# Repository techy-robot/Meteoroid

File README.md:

# Meteoroid

Production-ready 3d printer based on a Ender 5 frame, with multifunction tool changing, bed changing, and accessories with robots.

Preview Picture

Latest V0.7.0 [Onshape Link](https://cad.onshape.com/documents/1de0655c0501c319c0be82e5/v/c2a582b56fbe86c2e3bf18a1/e/f03e8779d1a8cc2741025c01)

It is desktop machine with plug and play heads. Chain these machines together and add robot carriages in between and you got yourself an awesome modular factory that can fit on a bench. The cost of the _entire system_ will likely be several thousand dollars, with the main machine between $300 to $500. I aim to lower the cost of a complete industrial system as much as possible.

The base machine is a CoreXY printer with a 500+mm/s move speed 30k+ accel, and 4 tool changer slots. The printer can be partially enclosed, with openings for robots to quick swap tools and beds and sometimes even sub-tools (Like a PnP head with different nozzle sizes). Software-wise, it will be running Klipper, which can interface with other software like OpenPNP using macros and linux ports.

Features:
- Standard 235mm x 235mm heated bed size with Garolyte bed for easy print release, supported by dual z-axis motors to provide stabilty without the complexity of an automatic leveling trimotor bed.
- Klipper
- Tool changer with 4 slots
- CoreXY
- Medium cost desktop production system
- Completely Open-Source
- 3 Accessory slots for extra toolhead elements like PnP heads or a camera
- Off-the-shelf components that are well known and high-quality, with many parts 3D printed in ASA
- Optional enclosure
- High print speed 500mm/s and 30k accel

I also designed a little adapter board I called Klipper to CACKLE. It basically takes USB-c input and 24v power, and converts this to my [CACKLE](https://github.com/techy-robot/CACKLE) layout spec and RS485 communication protocal. It uses a CH32 chip to process the commands and output equivalent Luos spec datapackets over the bus to my system.

# Building
I don't have specific build instructions yet as that takes a lot more development time, but you can reference the [BOM](https://github.com/techy-robot/Meteoroid/blob/main/BOM_Main%20assembly_simplified.csv) and the CAD file/Onshape to get all the parts and build it.

# Development Log
This project was worked on sporadically since Feb 1, 2025

See [Changelog](https://github.com/techy-robot/Meteoroid/blob/main/Changelog.md) for my full development log and the nitty-gritty details

# Credits
The motion system inspiration is from [Zero G Mercury 1.1](https://docs.zerog.one/manual/build/mercury_eva), which is a relatively simple corexy conversion for ender 5-style frames. I have tweaked many of the parts to fix small issues I noticed, revamped the frame with supports, added a toolchanging solution, and a 2 axis bed leveling system instead of the more costly 3-axis Hydra solution. The toolchanger is similar to the [Daksh V2](https://github.com/ankurv2k6/daksh-toolchanger-v2/) solution, except with a simpler single lock system, and concentric kinematic mount points instead of asymetrical contact mounts.

Everything else should be my own design, from the upcoming bed changing solution, upcoming robotic arms, toolheads, and the asteroid texture used on some of the parts.

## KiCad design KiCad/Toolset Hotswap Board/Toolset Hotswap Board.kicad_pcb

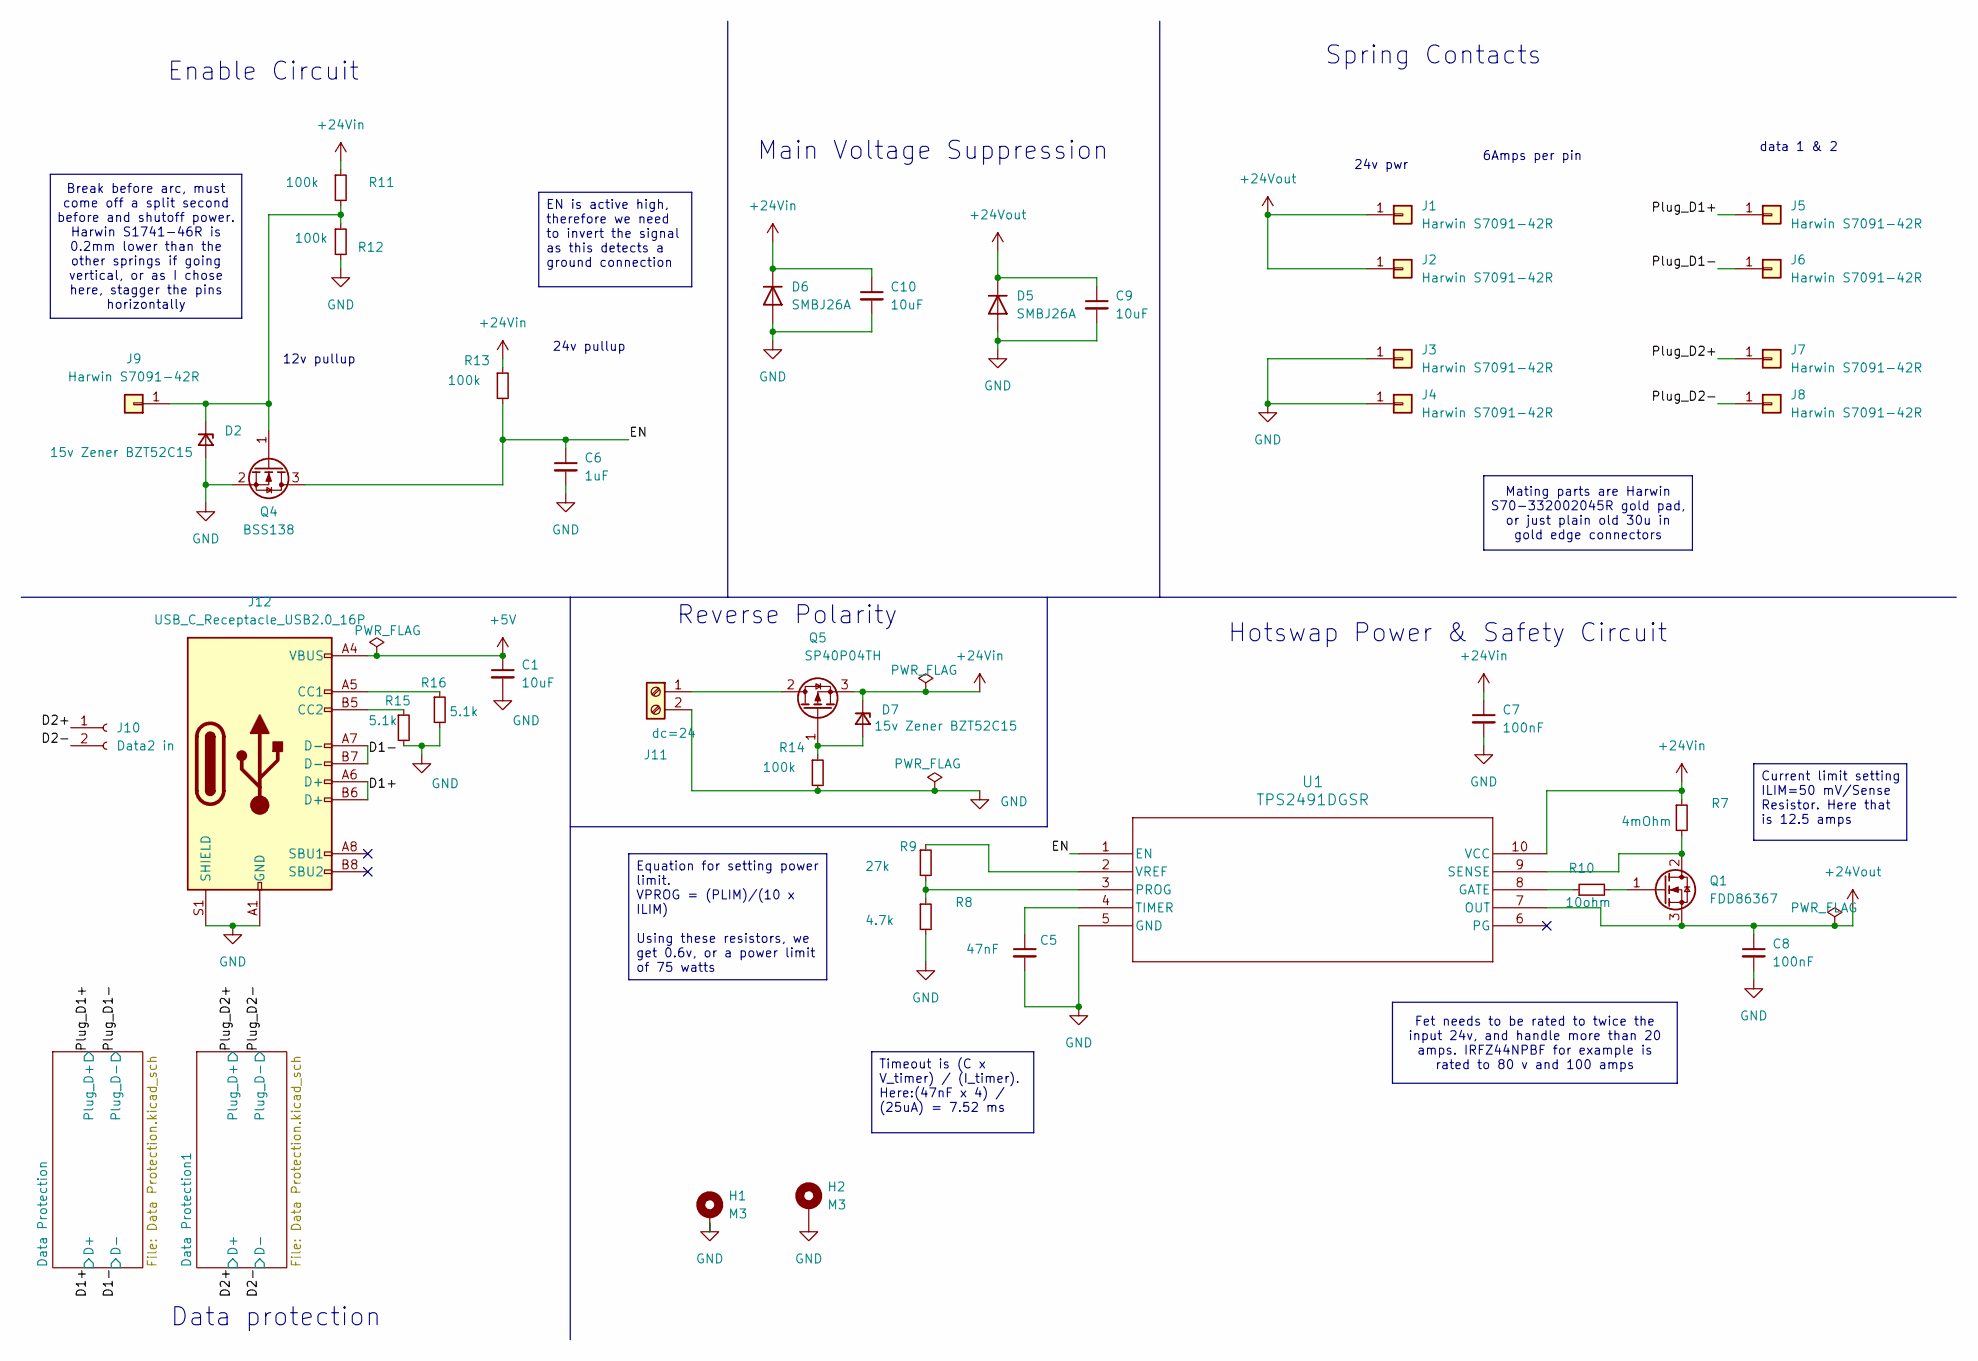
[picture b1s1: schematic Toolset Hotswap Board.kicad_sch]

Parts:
C1, C9, C10: 10uF; C_0805_2012Metric; LCSC C440198
C5: 47nF; C_0603_1608Metric; LCSC C1622
C6: 1uF; C_0603_1608Metric; LCSC C15849
C7, C8: 100nF; C_0402_1005Metric; LCSC C307331
D2, D7: 15v Zener BZT52C15; D_SOD-123; LCSC C2932746
D5, D6: SMBJ26A; D_SMB; LCSC C123820
H1, H2: M3; MountingHole_3.2mm_M3_Pad_Via
J1, J2, J3, J4, J5, J6, J7, J8, J9: Harwin S7091-42R; HARWIN_S7091-42R; LCSC C21394879
J10: Data2 in; PinSocket_1x02_P2.54mm_Vertical
J11: dc=24; TerminalBlock_CUI_TB007-508-02_1x02_P5.08mm_Horizontal; LCSC C430601
J12: USB_C_Receptacle_USB2.0_16P; USB_C_Receptacle_G-Switch_GT-USB-7010ASV; LCSC C2988369
Q1: FDD86367; TO-252-2; LCSC C903589
Q4: BSS138; SOT-23; LCSC C7420339
Q5: SP40P04TH; TO-252-2; LCSC C41355036
R7: 4mOhm; R_2512_6332Metric; LCSC C7420003
R8: 4.7k; R_0402_1005Metric; LCSC C25900
R9: 27k; R_0402_1005Metric; LCSC C25771
R10: 10ohm; R_0402_1005Metric; LCSC C25077
R11, R12, R13, R14: 100k; R_0402_1005Metric; LCSC C25741
R15, R16: 5.1k; R_0402_1005Metric; LCSC C25905
U1: TPS2491DGSR; VSSOP-10_3x3mm_P0.5mm; LCSC C273636

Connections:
+5V: C1.1, J12.A4 (VBUS), J12.A9 (VBUS), J12.B4 (VBUS), J12.B9 (VBUS); also elsewhere on the board
+24Vin: C7.1, C10.1, D6.1 (K), D7.1 (K), Q5.3 (S), R7.1, R11.1, R13.1, U1.10 (VCC); also elsewhere on the board
+24Vout: C8.1, C9.1, D5.1 (K), J1.1, J2.1, Q1.3 (S), U1.7 (OUT)
/D1+: J12.A6 (D+), J12.B6 (D+); also elsewhere on the board
/D1-: J12.A7 (D-), J12.B7 (D-); also elsewhere on the board
/D2+: J10.1; also elsewhere on the board
/D2-: J10.2; also elsewhere on the board
/EN: C6.1, Q4.3 (D), R13.2, U1.1 (EN)
/Plug_D1+: J5.1; also elsewhere on the board
/Plug_D1-: J6.1; also elsewhere on the board
/Plug_D2+: J7.1; also elsewhere on the board
/Plug_D2-: J8.1; also elsewhere on the board
GND: C1.2, C5.2, C6.2, C7.2, C8.2, C9.2, C10.2, D2.2 (A), D5.2 (A), D6.2 (A), H1.1, H2.1, J3.1, J4.1, J11.2, J12.A1 (GND), J12.A12 (GND), J12.B1 (GND), J12.B12 (GND), J12.S1 (SHIELD), Q4.2 (S), R8.2, R12.2, R14.2, R15.2, R16.2, U1.5 (GND); also elsewhere on the board
unnamed: D2.1 (K), J9.1, Q4.1 (G), R11.2, R12.1
unnamed: D7.2 (A), Q5.1 (G), R14.1
unnamed: J11.1, Q5.2 (D)
unnamed: J12.A5 (CC1), R16.1
unnamed: J12.B5 (CC2), R15.1
unnamed: Q1.2 (D), R7.2, U1.9 (SENSE)
unnamed: Q1.1 (G), R10.2
unnamed: R10.1, U1.8 (GATE)
unnamed: R8.1, R9.2, U1.3 (PROG)
unnamed: C5.1, U1.4 (TIMER)
unnamed: R9.1, U1.2 (VREF)

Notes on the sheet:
Enable Circuit
Main Voltage Suppression
data 1 & 2
24v pwr
Spring Contacts
6Amps per pin
Reverse Polarity
Data protection
24v pullup
Hotswap Power & Safety Circuit
12v pullup
Mating parts are Harwin S70-332002045R gold pad, or just plain old 30u in gold edge connectors
EN is active high, therefore we need to invert the signal as this detects a ground connection
Current limit setting ILIM=50 mV/Sense Resistor. Here that is 12.5 amps
Fet needs to be rated to twice the input 24v, and handle more than 20 amps. IRFZ44NPBF for example is rated to 80 v and 100 amps
Timeout is (C x V_timer) / (I_timer). Here:(47nF x 4) / (25uA) = 7.52 ms
Break before arc, must come off a split second before and shutoff power. Harwin S1741-46R is 0.2mm lower than the other springs if going vertical, or as I chose here, stagger the pins horizontally
Equation for setting power limit. VPROG = (PLIM)/(10 x ILIM) Using these resistors, we get 0.6v, or a power limit of 75 watts

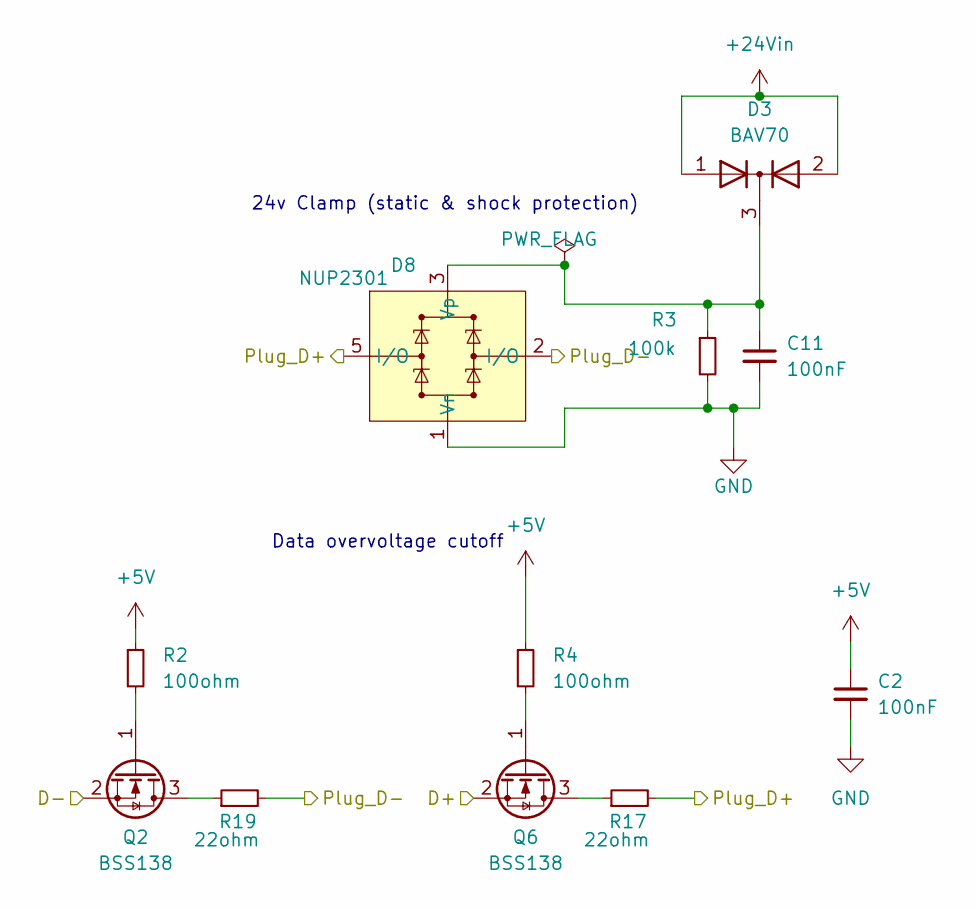
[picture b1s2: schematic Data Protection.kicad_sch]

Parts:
C2, C11: 100nF; C_0402_1005Metric; LCSC C307331
D3: BAV70; SOT-23; LCSC C68978
D8: NUP2301; SOT-363_SC-70-6; LCSC C708740
Q2, Q6: BSS138; SOT-23; LCSC C7420339
R2, R4: 100ohm; R_0402_1005Metric; LCSC C25076
R3: 100k; R_0402_1005Metric; LCSC C25741
R17, R19: 22ohm; R_0402_1005Metric; LCSC C25092

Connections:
+5V: C2.1, R2.1, R4.1; also elsewhere on the board
+24Vin: D3.1 (A), D3.2 (A); also elsewhere on the board
/D1+: Q6.2 (S); also elsewhere on the board
/D1-: Q2.2 (S); also elsewhere on the board
/Plug_D1+: D8.5 (I/O), R17.2; also elsewhere on the board
/Plug_D1-: D8.2 (I/O), R19.2; also elsewhere on the board
GND: C2.2, C11.2, D8.1 (Vn), R3.2; also elsewhere on the board
unnamed: C11.1, D3.3 (K), D8.3 (Vp), R3.1
unnamed: Q2.3 (D), R19.1
unnamed: Q2.1 (G), R2.2
unnamed: Q6.3 (D), R17.1
unnamed: Q6.1 (G), R4.2

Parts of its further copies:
C3, C12: 100nF; C_0402_1005Metric; LCSC C307331
D1: BAV70; SOT-23; LCSC C68978
D9: NUP2301; SOT-363_SC-70-6; LCSC C708740
Q3, Q7: BSS138; SOT-23; LCSC C7420339
R1: 100k; R_0402_1005Metric; LCSC C25741
R5, R6: 100ohm; R_0402_1005Metric; LCSC C25076
R18, R20: 22ohm; R_0402_1005Metric; LCSC C25092

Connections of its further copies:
+5V: C3.1, R5.1, R6.1; also elsewhere on the board
+24Vin: D1.1 (A), D1.2 (A); also elsewhere on the board
/D2+: Q7.2 (S); also elsewhere on the board
/D2-: Q3.2 (S); also elsewhere on the board
/Plug_D2+: D9.5 (I/O), R18.2; also elsewhere on the board
/Plug_D2-: D9.2 (I/O), R20.2; also elsewhere on the board
GND: C3.2, C12.2, D9.1 (Vn), R1.2; also elsewhere on the board
unnamed: C12.1, D1.3 (K), D9.3 (Vp), R1.1
unnamed: Q3.3 (D), R20.1
unnamed: Q3.1 (G), R5.2
unnamed: Q7.3 (D), R18.1
unnamed: Q7.1 (G), R6.2

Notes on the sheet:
Data overvoltage cutoff
24v Clamp (static & shock protection)

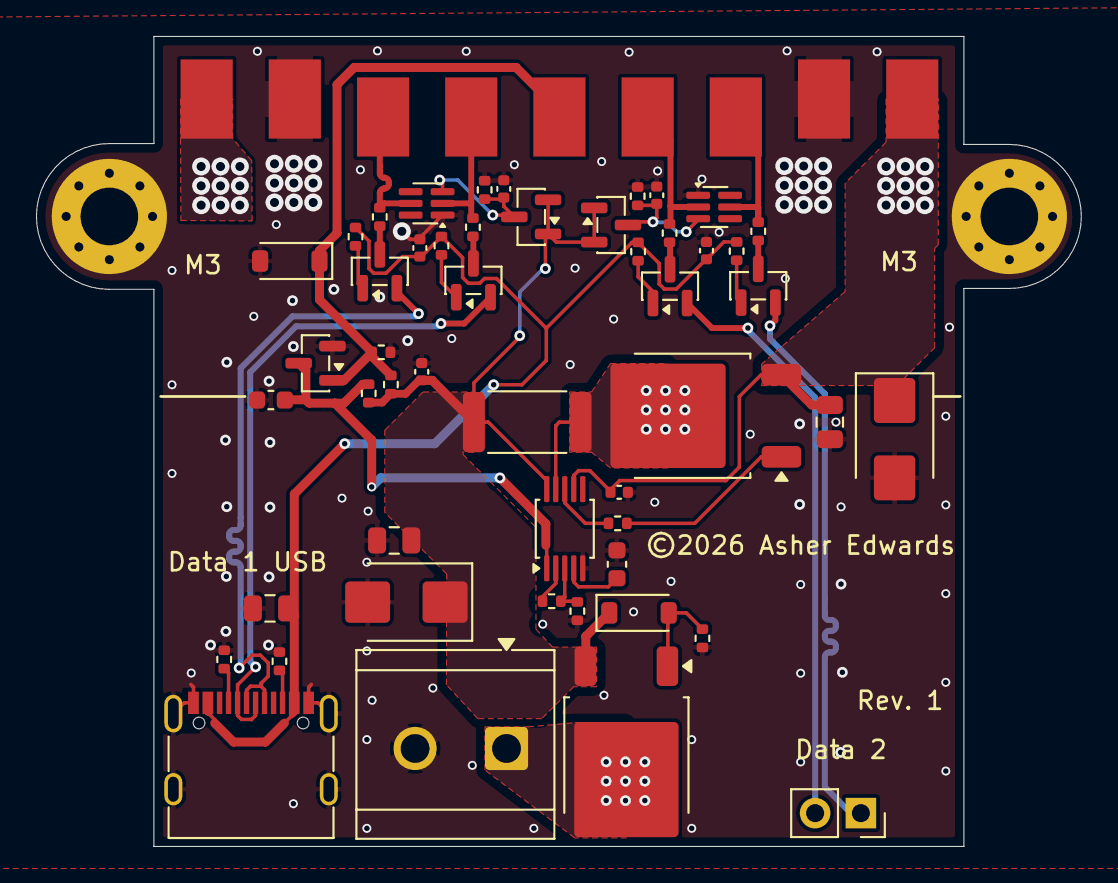
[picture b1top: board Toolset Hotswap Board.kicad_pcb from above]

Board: 2 copper layers, 58.0 x 45.0 mm, 61 parts (0 on the bottom side), 34 nets.

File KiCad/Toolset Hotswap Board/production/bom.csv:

Designator,Footprint,Quantity,Value,LCSC Part #
"C1, C10, C9",0805,3,10uF,C440198
"C11, C12, C2, C3, C7, C8",0402,6,100nF,C307331
C5,0603,1,47nF,C1622
C6,0603,1,1uF,C15849
"D1, D3",SOT-23,2,BAV70,C68978
"D2, D7",D_SOD-123,2,15v Zener BZT52C15,C2932746
"D5, D6",D_SMB,2,SMBJ26A,C123820
"D8, D9",SOT-363_SC-70-6,2,NUP2301,C708740
"J1, J2, J3, J4, J5, J6, J7, J8, J9",HARWIN_S7091-42R,9,Harwin S7091-42R,C21394879
J10,PinSocket_1x02_P2.54mm_Vertical,1,Data2 in,
J11,TerminalBlock_CUI_TB007-508-02_1x02_P5.08mm_Horizontal,1,dc=24,C430601
J12,USB_C_Receptacle_G-Switch_GT-USB-7010ASV,1,USB_C_Receptacle_USB2.0_16P,C2988369
Q1,TO-252-2,1,FDD86367,C903589
"Q2, Q3, Q4, Q6, Q7",SOT-23,5,BSS138,C7420339
Q5,TO-252-2,1,SP40P04TH,C41355036
"R1, R11, R12, R13, R14, R3",0402,6,100k,C25741
R10,0402,1,10ohm,C25077
"R15, R16",0402,2,5.1k,C25905
"R17, R18, R19, R20",0402,4,22ohm,C25092
"R2, R4, R5, R6",0402,4,100ohm,C25076
R7,2512,1,4mOhm,C7420003
R8,0402,1,4.7k,C25900
R9,0402,1,27k,C25771
U1,VSSOP-10_3x3mm_P0.5mm,1,TPS2491DGSR,C273636

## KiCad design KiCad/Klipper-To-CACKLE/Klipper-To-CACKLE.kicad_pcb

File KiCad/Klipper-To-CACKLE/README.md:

---
modified: 2025-04-05T19:11:32-07:00
---

# Klipper to Cackle

This is a simple adapter board PSU that takes 24v in and usb, and outputs a CACKLE compatible form factor and RS485 Luos commands.

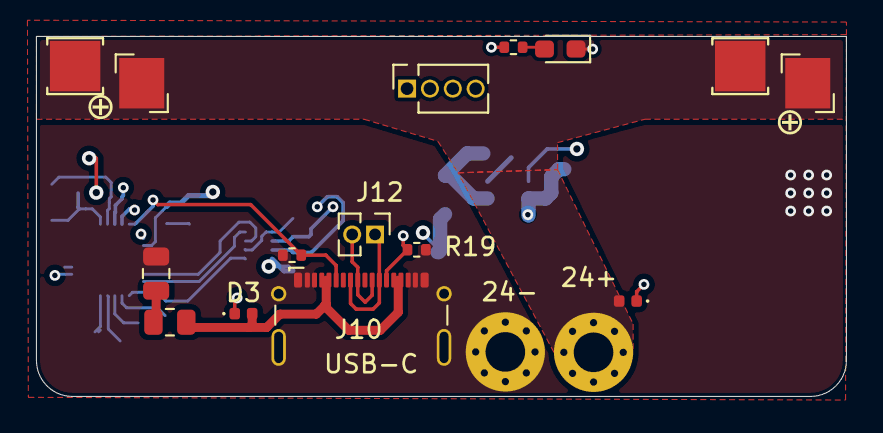
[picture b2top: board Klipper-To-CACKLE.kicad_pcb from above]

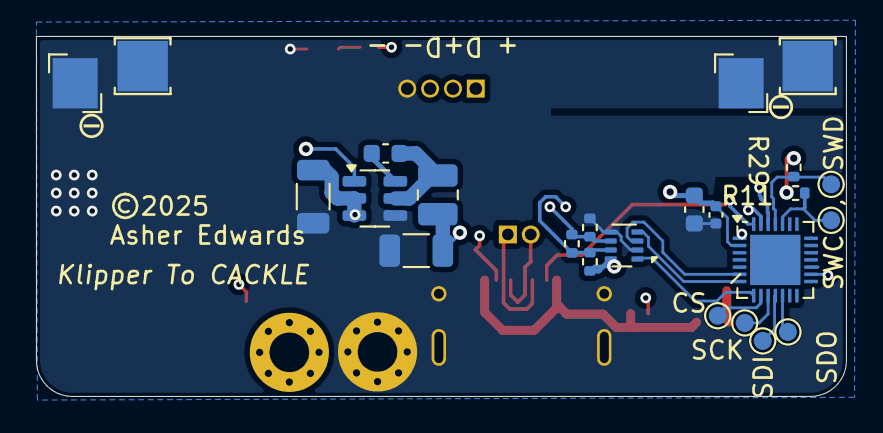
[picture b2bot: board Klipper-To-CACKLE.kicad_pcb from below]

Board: 4 copper layers, 45.0 x 20.0 mm, 41 parts (25 on the bottom side), 25 nets.

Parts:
C7: 10uF, 16v; C_0805_2012Metric
C25: 100nF, 16v; C_0402_1005Metric
C26: 4.7uF, 16v; C_0603_1608Metric
C27: 22uf, 16v CL31A226MOCLNN; C_1206_3216Metric
C28: 22uf, 32v; C_1206_3216Metric
C40: 100nF, 16v; C_0603_1608Metric
D2, D3: GSDH3005; D_0402_1005Metric
D4: 2.6~3.1 Fv Green 5ma; LED_0603_1608Metric_Pad1.05x0.95mm_HandSolder
H1: HIGHPWR; MountingHole_2.2mm_M2_Pad_Via
H2: HIGHGND; MountingHole_2.2mm_M2_Pad_Via
J1, J3, J6, J7: Keystone 3579; Keystone_3579
J4, J5, J8, J9: Keystone 3569; Keystone_3569_half
J10: G-Switch-GT-USB-7025; USB_C_G-Switch_GT-USB-7025-JLCPCBv
J11: 1.27mm 4 pin socket; PinSocket_1x04_P1.27mm_Vertical
J12: USB; PinHeader_1x02_P1.27mm_Vertical
L3: 2.2uH, WIP322512A-2R2MLDG; L_1008_2520Metric
R2: 2ohm; R_0805_2012Metric
R11, R29: 10k; R_0402_1005Metric
R19, R33: 5.1k; R_0402_1005Metric
R25: 80.6 ohm; R_0402_1005Metric
R26, R27, R28: 120 ohm; R_0402_1005Metric
TP1: SWC; TestPoint_Pad_D1.0mm
TP2: CS; TestPoint_Pad_D1.0mm
TP3: SCK; TestPoint_Pad_D1.0mm
TP4: SWD; TestPoint_Pad_D1.0mm
TP5: SDI; TestPoint_Pad_D1.0mm
TP6: SDO; TestPoint_Pad_D1.0mm
U2: AP63203WU; TSOT-23-6
U5: THVD1420DRLR; SOT-583-8
U6: CH32X035G8U6; QFN-28-1EP_4x4mm_P0.4mm_EP2.8x2.8mm

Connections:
/Connectors/3.3v: C25.1, C26.1, C27.1, J11.1, L3.2, R11.2, R28.1, R29.2, U2.1 (FB), U5.8 (VCC), U6.2 (VDD)
/Connectors/CC1: J10.A5 (CC1), R33.2, U6.28 (CC1/PC14)
/Connectors/CC2: J10.B5 (CC2), R19.2, U6.1 (CC2/PC15)
/Connectors/D+: J10.A6 (D+), J10.B6 (D+), J12.1, U6.27 (USB1_DP/PC17)
/Connectors/D-: J10.A7 (D-), J10.B7 (D-), J12.2, U6.26 (USB1_DM/PC16)
/Connectors/HIGHPWR: D2.2 (A), H1.1, J1.1, J3.1, J4.1, J5.1
/Connectors/RS485+: J11.2, R27.2, R28.2, U5.7 (B)
/Connectors/RS485-: J11.3, R26.1, R27.1, U5.6 (A)
/Connectors/USBPWR: D3.2 (A), J10.A4 (VBUS), J10.A9 (VBUS), J10.B4 (VBUS), J10.B9 (VBUS), R2.2
/MCU/CS: TP2.1, U6.9 (ADC4/PA4)
/MCU/LED: R25.1, U6.16 (PB1/PB5/ADC9)
/MCU/MISO: TP5.1, U6.11 (ADC6/PA6)
/MCU/MOSI: TP6.1, U6.12 (ADC7/PA7)
/MCU/SCLK: TP3.1, U6.10 (ADC5/PA5)
/MCU/UART1-RTS: U5.3 (DE), U6.6 (ADC1/PA1)
/MCU/UART1_RX: U5.1 (RO), U6.8 (ADC3/PA3)
/MCU/UART1_TX: U5.4 (DI), U6.7 (ADC2/PA2)
/PSU/Always On PWR: C28.1, D2.1 (K), D3.1 (K), U2.2 (EN), U2.3 (IN)
/SCL: R11.1, TP1.1, U6.24 (SWCLK/PC19)
/SDA: R29.1, TP4.1, U6.25 (SWDIO/PC18)
GND: C7.2, C25.2, C26.2, C27.2, C28.2, D4.1 (K), H2.1, J6.1, J7.1, J8.1, J9.1, J10.A1 (GND), J10.A12 (GND), J10.B1 (GND), J10.B12 (GND), J10.GND, J10.S1 (SHIELD), J11.4, R19.1, R26.2, R33.1, U2.4 (GND), U5.2 (~RE), U5.5 (GND), U6.29 (GND)
unnamed: C7.1, R2.1
unnamed: D4.2 (A), R25.2
unnamed: C40.1, U2.6 (BST)
unnamed: C40.2, L3.1, U2.5 (SW)

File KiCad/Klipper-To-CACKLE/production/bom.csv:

Designator,Footprint,Quantity,Value,LCSC Part #
C25,0402,1,"100nF, 16v",C1525
C26,0603,1,"4.7uF, 16v",C19666
C27,1206,1,"22uf, 16v CL31A226MOCLNN",C159758
C28,1206,1,"22uf, 32v",C159758
C40,0603,1,"100nF, 16v",C14663
C7,0805,1,"10uF, 16v",C15850
"D2, D3",0402,2,GSDH3005,C2837790
D4,0603,1,2.6~3.1 Fv Green 5ma,C3028858
"J1, J3, J6, J7",Keystone_3579,4,Keystone 3579,
J10,USB_C_G-Switch_GT-USB-7025-JLCPCBv,1,G-Switch-GT-USB-7025,C963213
J11,PinSocket_1x04_P1.27mm_Vertical,1,1.27mm 4 pin socket,
"J4, J5, J8, J9",Keystone_3569_half,4,Keystone 3569,
L3,1008,1,"2.2uH, WIP322512A-2R2MLDG",C5832372
"R11, R29",0402,2,10k,C25744
"R19, R33",0402,2,5.1k,C25905
R2,0805,1,2ohm,C17521
R25,0402,1,80.6 ohm,C185392
"R26, R27, R28",0402,3,120 ohm,C25079
U2,TSOT-23-6,1,AP63203WU,C780769
U5,SOT-583-8,1,THVD1420DRLR,
U6,QFN-28-1EP_4x4mm_P0.4mm_EP2.8x2.8mm,1,CH32X035G8U6,C7437027

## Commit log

2025-02-05 Updated Ideas and README
2025-02-06 Update Changelog.md with Goals
2025-02-26 Back at designing
    Hope the image link doesn't break vercel!
2025-02-26 Update Changelog.md
    fixed link for github viewing
2025-03-01 Update Changelog.md with info on header
2025-03-06 Updated Log with logo ideas and frame
2025-03-06 Fixed image link
2025-03-09 Finished Logo Design
2025-03-09 Uploaded png version of logo
2025-03-09 Updated License for Artwork and drawings
2025-03-10 Added Frame Stiffener
2025-03-18 Add Z-axis rails to frame
2025-03-19 Start bed frame design
2025-03-23 Updated Icon
2025-03-23 Updated changelog to point to old version of logo
    I need to see the change!
2025-03-25 Added main CAD file, finished base frame
2025-03-25 Fixed broken image link
2025-03-28 Finished x axis, changed color scheme
    forgot to commit it yesterday though!
2025-03-28 Added reference pictures
2025-03-28 Updated CAD step files with latest colors and x joint
2025-03-28 Fixed another broken image link
2025-03-28 Organizing docs
2025-03-28 Added Obsidian md settings file
2025-03-29 3 Days Left! Finished main motion, still need toolheads
2025-03-31 Finished toolhead carriage and lock
2025-04-03 Finished Toolhead design
2025-04-05 Pre-prep for v0.5
2025-04-06 Push for v0.5
    added pcb and docs
2025-04-06 Rename CACKLE_2s_40A_PSU__Charger_V1.zip to Klipper-To-CACKLE.zip
2025-04-06 Rename CACKLE_2s_40A_PSU__Charger_V1_2025-04-06_00-21-42.zip to Klipper-To-CACKLE_2025-04-06_00-21-42.zip
2025-04-06 Updated BOM
2025-04-07 Redesigned XY Gantry
2025-04-07 Updated description and pictures
2025-04-07 Fixed Changelog Pictures
2025-04-07 Updated link
2025-04-07 Updated hours
2025-04-21 Minor clearance changes
2025-04-21 Updated changelog
2025-04-21 Started printer file config
2025-04-21 Adjusted tolerances
2025-04-22 Fixed toolhead missing lock entrance
2025-04-29 Updated log
2025-05-04 Redesigned toolhead
2025-05-04 Made ducts thinner
2025-05-04 Updated print project
2025-05-06 Fixed motor mount hole size
    It was too small to account for a rim on the motor
2025-05-12 Added Chamber
2025-05-28 Getting ready for v0.7
2025-05-28 Updated pictures
2025-07-10 Added CONTRIBUTING
2025-07-10 fixed track gap
2025-07-10 2nd prototype push push lock
2025-07-10 first prototype of push push lock
2025-07-10 rotated springs 90 degrees, redesigned tracks slightly
2025-07-10 added teardrops to lock block
2025-07-10 re-added mounting contacts, tweaked clearances
2026-04-25 Fixed broken link
2026-04-25 Complete hotswap power & data board design
    IDK why I didn't commit this until now
2026-04-25 Massive CAD file dump from a year
2026-04-25 Ignore obsidian folder
2026-04-25 Ignore stop tracking obsidian
2026-04-25 Minor tweaks to adapter PCB from while back

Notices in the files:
KiCad/Klipper-To-CACKLE/Klipper-To-CACKLE.kicad_pcb:
Licensed under CERN-OHL-S
©2025
KiCad/Toolset Hotswap Board/Toolset Hotswap Board.kicad_pcb:
©2026 Asher Edwards
